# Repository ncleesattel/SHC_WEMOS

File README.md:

# SHC_WEMOS
This is a handheld controller for TeenAstro.  
See also [Link to TeenAstro Wiki](https://groups.io/g/TeenAstro/wiki) and [link to TeenAstro github](https://github.com/charleslemaire0/TeenAstro)   
  
It features a 3.3V OLED 2.42" display, a joystick together with the WEMOS D1 mini MCU.  
The associated pcb can be ordered at JLCPCB fully assembled with smd parts and JST XH connectors.  
This reduces the amount of soldering to a minimum.  
  
I also provide a design of an OLED pcb, that does not require smd soldering for the I2C use compared to the DIYmore pcb.  
Costs for the separate OLED pcb are about 3x, which makes it interesting only for hobbyists who want to avoid the smd solder.

## recommendations
* You’ll need to be able to solder a connection using a pinheader between the two pcbs.
* You’ll also need the soldering iron to melt the Ruthex nuts into place.
* The 3D prints do not need supports. Depending on your printer you may need to scale by 1.015 to account for thermal shrink.
* The cable length should be properly sized. The case does not have much room to accommodate long cables, however short cables make assembly and disassembly more difficult.
* Although the JST XH connectors can be attached to the cables without a crimp tool, I would highly recommend one for ease of life. You can thank me later.
*Check the functionality and connector sequence/polarity prior to assembly.

## components needed for build
* PCB group
  * pcb incl. smd parts of SHC
  * pcb for OLED 2.42“. Either mine with switches for I2C or DIYmore incl. smd modification
  * OLED 2.42“ display
  * metal bracket to attach OLED display to OLED pcb
* 3D print group
  * 3d print for pcb to display spacer
  * 3d print of bottom part
  * 3d print of top cover
  * Ruthex M3 nuts 2x
* Switches and cables
  * APEM 1000 joystick
  * APEM 1212 switch for shift
  * RAFI switches for focusser
  * SAL8 connector
  * JST XH connectors

## which files are needed for the...
* pcbs
  * SHC pcb --> jlcpcb folder
  * OLED pcb --> separate repository
* 3D prints
  * SHC bottom case --> models folder
  * SHC top case --> models folder
  * SHC display to pcb spacer --> models folder
 
 ## associated CAD files
The CAD files have been mostly created in Fusion 360 with OEM parts imported where available.

## approximate cost
The cost is calculated for a single SHC, assuming the pcb cost of 5 can be shared.
Shipping costs are included for 2x JLCPCB and 1x Reichelt.

| Parts | Cost |
|-------|------|
| WEMOS D1 mini | 6€ |
| 3d printed parts | 40€ |
| SHC pcb | 8€ |
| OLED pcb | 8€ |
| OLED with frame | 18€ |
| APEM joystick | 32€ |
| RAFI and APEM switches | 9€ |
| Remainder | 10€ |
| Total | 131€ |

Depending on if you have access to a 3d printer and can share the pcb cost, you're looking the following range:
minimal build cost 90€ (own 3d printer and can share pcb cost)
maximal build cost 180€ (have to order the 3d case stls and cannot share pcb cost)

## pictures of the SHC

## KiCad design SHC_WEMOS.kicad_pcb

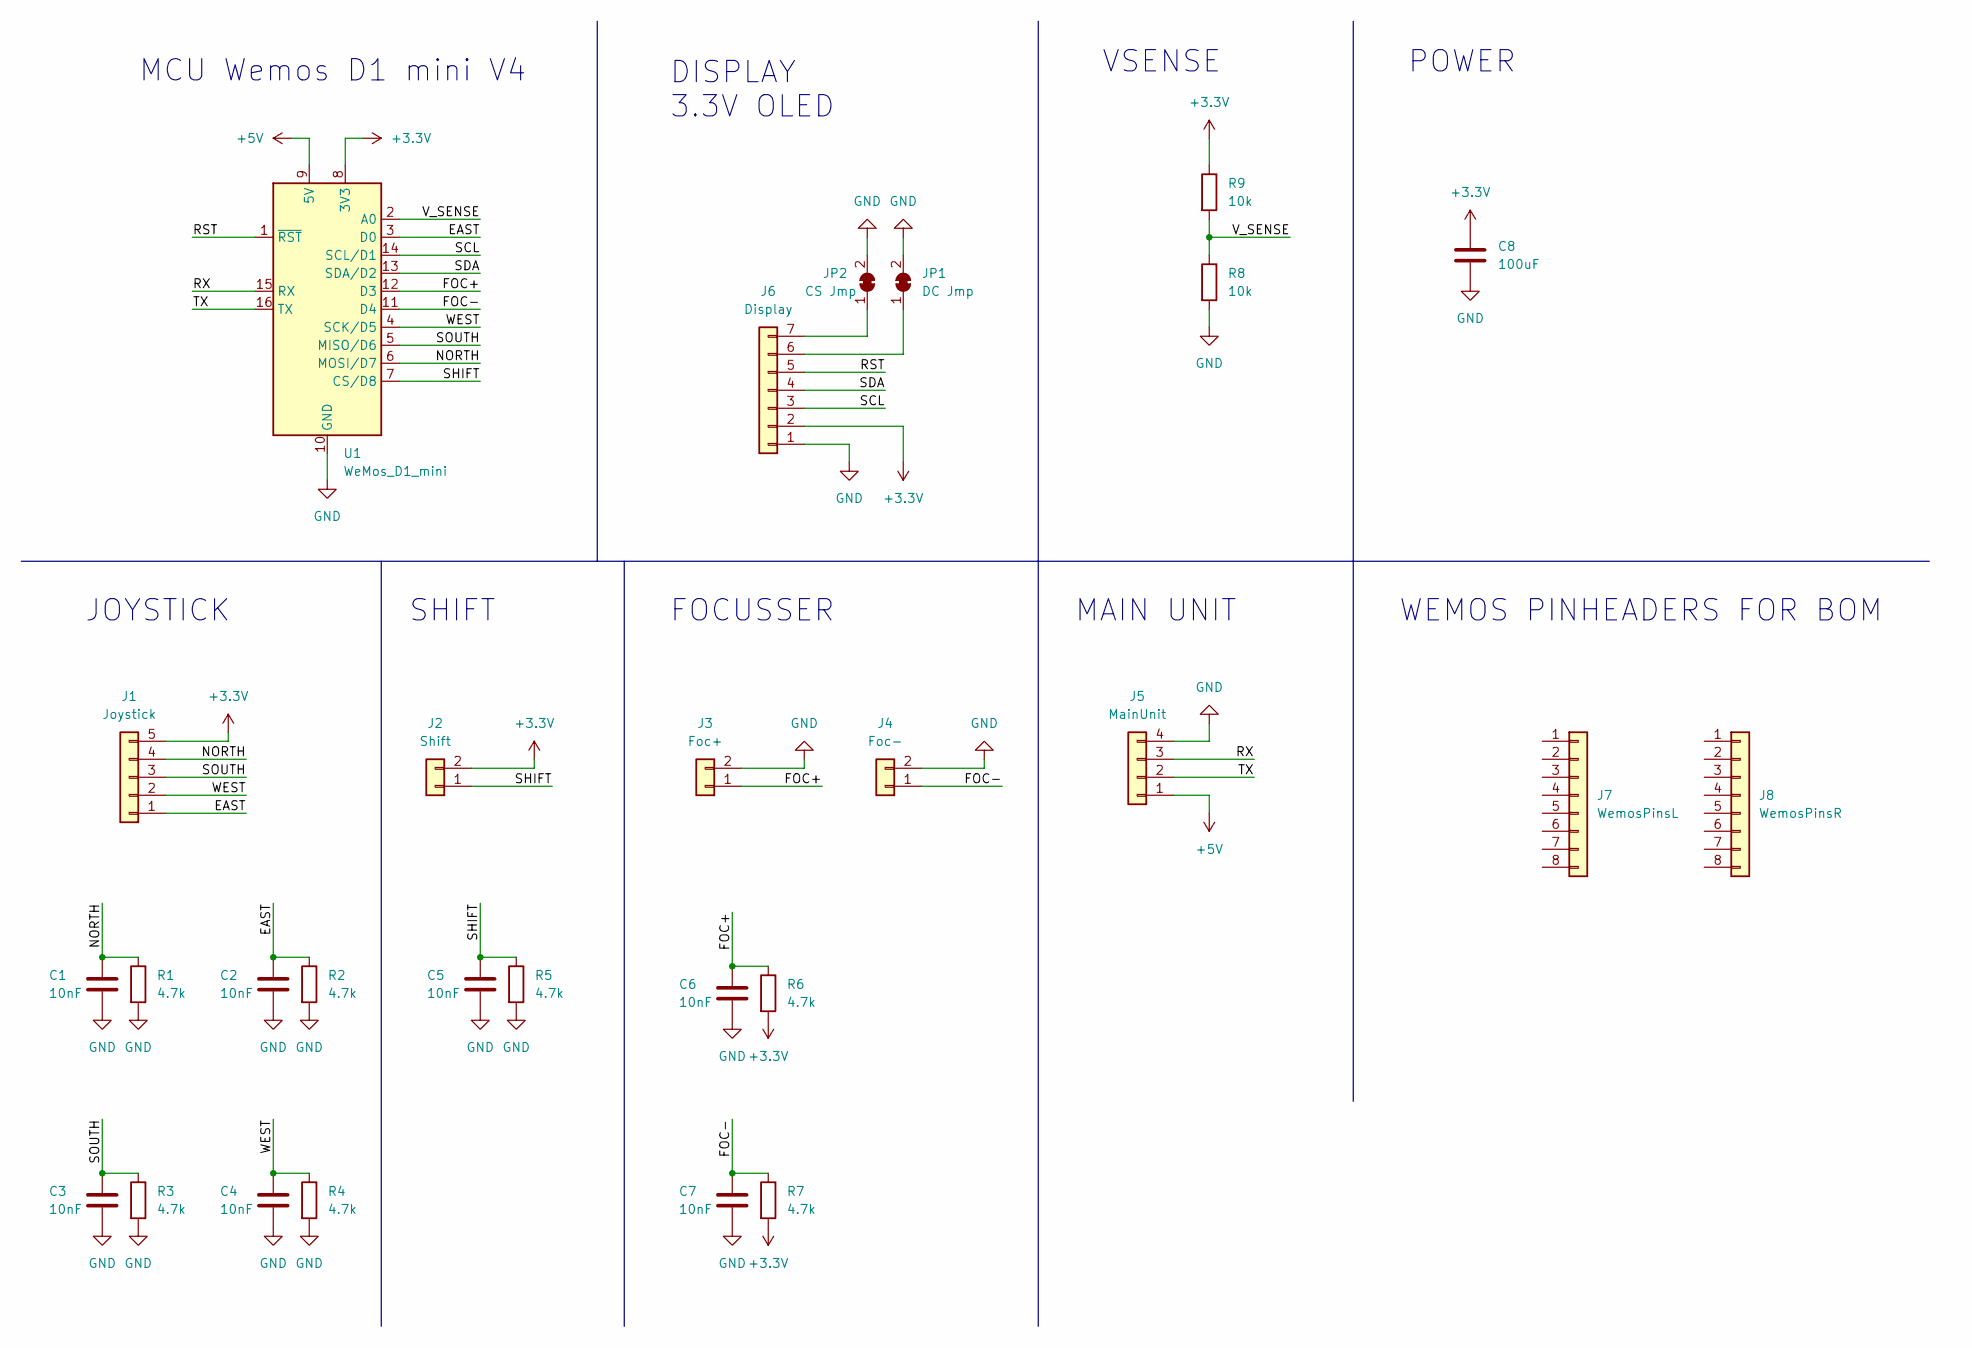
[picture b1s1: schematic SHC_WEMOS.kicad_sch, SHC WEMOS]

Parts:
C1, C2, C3, C4, C5, C6, C7: 10nF; C_0805_2012Metric; LCSC C1710
C8: 100uF; C_1206_3216Metric; LCSC C15008
J1: Joystick; JST_XH_S5B-XH-A_1x05_P2.50mm_Horizontal; LCSC C263757
J2: Shift; JST_XH_S2B-XH-A_1x02_P2.50mm_Horizontal; LCSC C157931
J3: Foc+; JST_XH_S2B-XH-A_1x02_P2.50mm_Horizontal; LCSC C157931
J4: Foc-; JST_XH_S2B-XH-A_1x02_P2.50mm_Horizontal; LCSC C157931
J5: MainUnit; JST_XH_S4B-XH-A_1x04_P2.50mm_Horizontal; LCSC C157925
J6: Display; PinHeader_1x07_P2.54mm_Vertical
J7: WemosPinsL; PinSocket_1x08_P2.54mm_Vertical; LCSC C27438
J8: WemosPinsR; PinSocket_1x08_P2.54mm_Vertical; LCSC C27438
JP1: DC Jmp; SolderJumper-2_P1.3mm_Bridged_RoundedPad1.0x1.5mm
JP2: CS Jmp; SolderJumper-2_P1.3mm_Bridged_RoundedPad1.0x1.5mm
R1, R2, R3, R4, R5, R6, R7: 4.7k; R_0603_1608Metric; LCSC C25999
R8, R9: 10k; R_0402_1005Metric; LCSC C25744
U1: WeMos_D1_mini; WEMOS_D1_mini_light

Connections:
+3.3V: C8.1, J1.5, J2.2, J6.2, R6.2, R7.2, R9.1, U1.8 (3V3)
+5V: J5.1, U1.9 (5V)
/EAST: C2.1, J1.1, R2.1, U1.3 (D0)
/FOC+: C6.1, J3.1, R6.1, U1.12 (D3)
/FOC-: C7.1, J4.1, R7.1, U1.11 (D4)
/NORTH: C1.1, J1.4, R1.1, U1.6 (MOSI/D7)
/RST: J6.5, U1.1 (~RST)
/RX: J5.3, U1.15 (RX)
/SCL: J6.3, U1.14 (SCL/D1)
/SDA: J6.4, U1.13 (SDA/D2)
/SHIFT: C5.1, J2.1, R5.1, U1.7 (CS/D8)
/SOUTH: C3.1, J1.3, R3.1, U1.5 (MISO/D6)
/TX: J5.2, U1.16 (TX)
/V_SENSE: R8.1, R9.2, U1.2 (A0)
/WEST: C4.1, J1.2, R4.1, U1.4 (SCK/D5)
GND: C1.2, C2.2, C3.2, C4.2, C5.2, C6.2, C7.2, C8.2, J3.2, J4.2, J5.4, J6.1, JP1.2 (B), JP2.2 (B), R1.2, R2.2, R3.2, R4.2, R5.2, R8.2, U1.10 (GND)
unnamed: J6.6, JP1.1 (A)
unnamed: J6.7, JP2.1 (A)

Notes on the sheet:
MCU Wemos D1 mini V4
MAIN UNIT
SHIFT
FOCUSSER
VSENSE
DISPLAY 3.3V OLED
WEMOS PINHEADERS FOR BOM
JOYSTICK
POWER

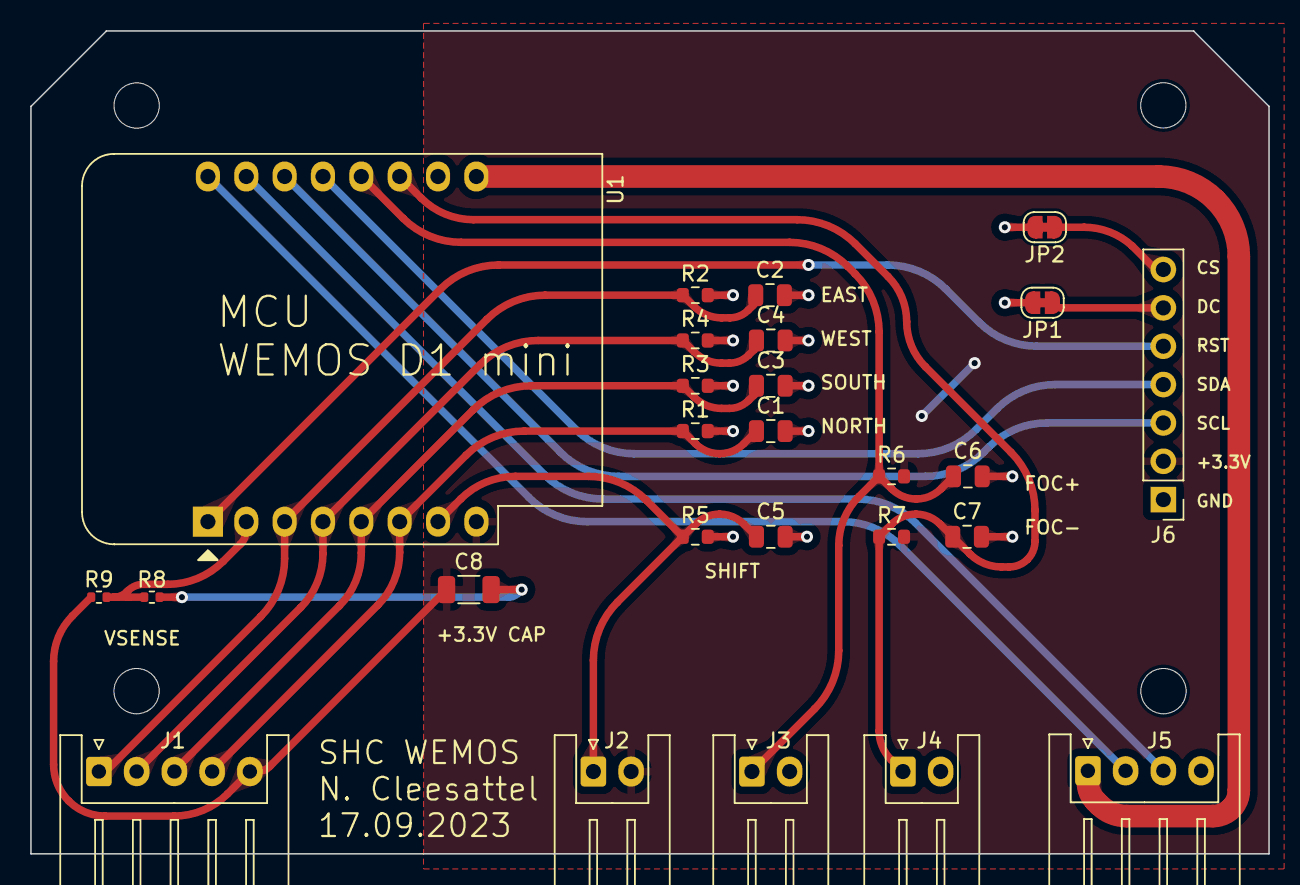
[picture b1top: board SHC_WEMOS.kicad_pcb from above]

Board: 2 copper layers, 82.0 x 54.5 mm, 26 parts (0 on the bottom side), 18 nets.

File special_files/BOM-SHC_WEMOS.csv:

Comment,Designator,Footprint,LCSC
100uF,C8,C_1206_3216Metric,C15008
MainUnit,J5,JST_XH_S4B-XH-A_1x04_P2.50mm_Horizontal,C157925
Shift,"J2,J3,J4",JST_XH_S2B-XH-A_1x02_P2.50mm_Horizontal,C157931
10nF,"C1,C2,C3,C4,C5,C6,C7",C_0805_2012Metric,C1710
10k,"R8,R9",R_0402_1005Metric,C25744
4.7k,"R1,R2,R3,R4,R5,R6,R7",R_0603_1608Metric,C25999
Joystick,J1,JST_XH_S5B-XH-A_1x05_P2.50mm_Horizontal,C263757
WemosPinsL,"J7,J8",PinSocket_1x08_P2.54mm_Vertical,C27438

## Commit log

2023-09-19 Initial release
    Initial release from private repository.
2023-09-19 Update README.md
    Update paths for images to new repo
2023-09-19 Add electric scheme as PDF print from KiCad
2023-09-20 Update README.md
    Added build cost estimate
